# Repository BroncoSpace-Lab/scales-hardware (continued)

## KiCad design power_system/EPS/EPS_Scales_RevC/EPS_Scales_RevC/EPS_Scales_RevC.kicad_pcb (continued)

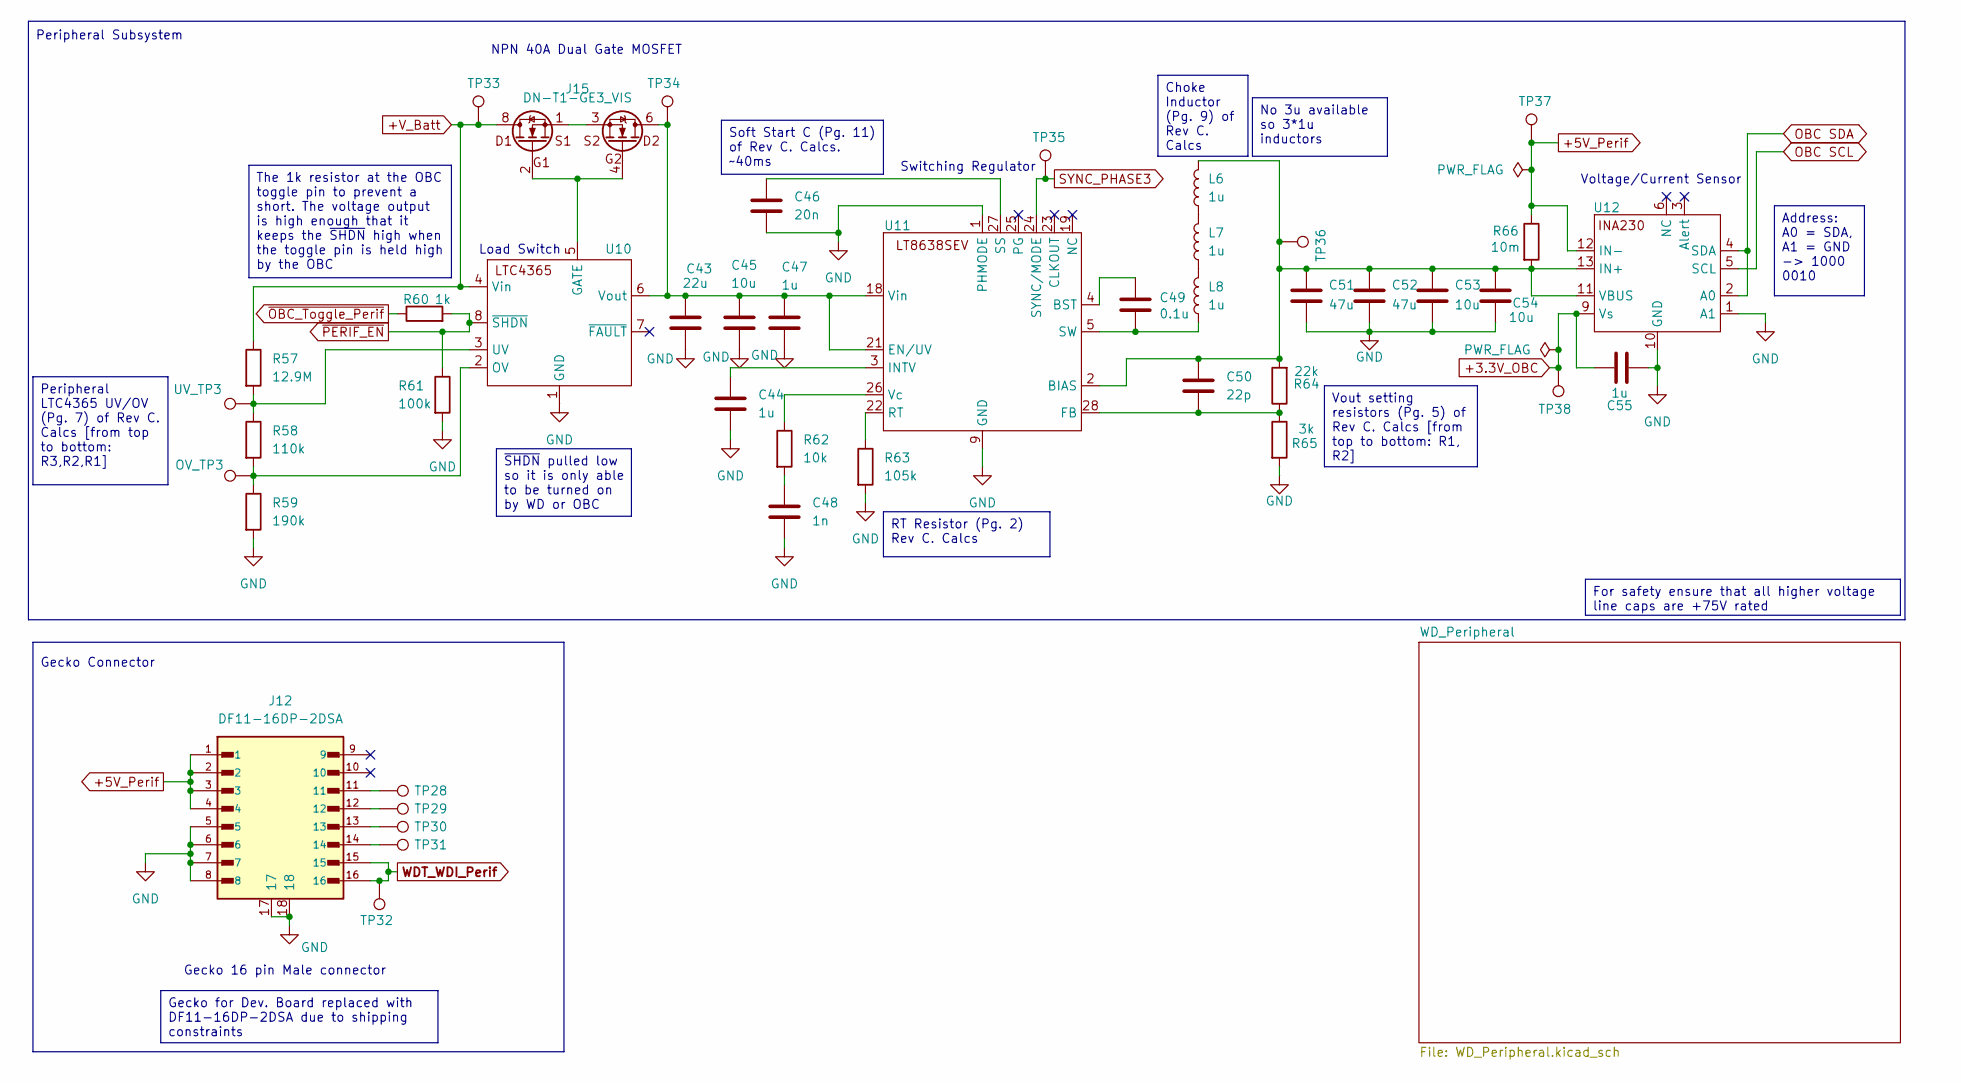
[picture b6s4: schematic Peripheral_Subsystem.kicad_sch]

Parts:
C43: 22u; C_1210_3225Metric; LCSC C309062
C44: 1u; C_0603_1608Metric; LCSC C304010
C45, C53, C54: 10u; C_1210_3225Metric
C46: 20n; C_0603_1608Metric; LCSC C87721
C47, C55: 1u; C_1210_3225Metric; LCSC C304010
C48: 1n; C_0603_1608Metric; LCSC C2173372
C49: 0.1u; C_1210_3225Metric; LCSC C436244
C50: 22p; C_1210_3225Metric
C51, C52: 47u; C_1210_3225Metric
J12: DF11-16DP-2DSA; DF1116DP2DSA08
J15: DN-T1-GE3_VIS; MOSFET_DN-T1-GE3_VIS
L6, L7, L8: 1u; XEL6030102MEC; LCSC C5157561
OV_TP3: TestPoint; TestPoint_Pad_1.0x1.0mm
R57: 12.9M; R_0603_1608Metric
R58: 110k; R_0603_1608Metric; LCSC C25805
R59: 190k; R_0603_1608Metric; LCSC C25811
R60: 1k; R_0603_1608Metric; LCSC C13163
R61: 100k; R_0603_1608Metric; LCSC C14675
R62: 10k; R_0603_1608Metric; LCSC C13564
R63: 105k; R_0603_1608Metric; LCSC C16840
R64: 22k; R_0603_1608Metric; LCSC C23344
R65: 3k; R_0603_1608Metric
R66: 10m; R_2512_6332Metric
TP28, TP29, TP30, TP31, TP32, TP33, TP34, TP35, TP36, TP37, TP38: TestPoint; TestPoint_Pad_1.0x1.0mm
U10: LTC4365; LCSC C580882
U11: LT8638S; LT8638SEVPBF
U12: INA230; INA230AIRGTT
UV_TP3: TestPoint; TestPoint_Pad_1.0x1.0mm

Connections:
+5V_Perif: J12.1, J12.2, J12.3, J12.4, R66.1, TP37.1, U12.12 (IN-); also elsewhere on the board
+V_Batt: J15.7, J15.8, R57.1, TP33.1, U10.4 (Vin); also elsewhere on the board
GND: C43.2, C44.2, C45.2, C46.2, C47.2, C48.2, C51.2, C52.2, C53.2, C54.2, C55.1, J12.5, J12.6, J12.7, J12.8, J12.17, J12.18, R59.2, R61.2, R63.2, R65.2, U10.1 (GND), U11.1 (PHMODE), U11.9 (GND), U12.1 (A1), U12.10 (GND); also elsewhere on the board
unnamed: C48.1, R62.2
unnamed: J12.11, TP28.1
unnamed: J12.12, TP29.1
unnamed: J12.13, TP30.1
unnamed: J12.14, TP31.1
unnamed: J15.1, J15.3
unnamed: L6.1, L7.2
unnamed: L7.1, L8.2
unnamed: J15.2, J15.4, U10.5 (GATE)
unnamed: OV_TP3.1, R58.2, R59.1, U10.2 (OV)
unnamed: R57.2, R58.1, U10.3 (UV), UV_TP3.1
unnamed: C43.1, C45.1, C47.1, J15.5, J15.6, TP34.1, U10.6 (Vout), U11.18 (Vin), U11.21 (EN/UV)
unnamed 93: C50.1, C51.1, C52.1, C53.1, C54.1, L6.2, R64.2, R66.2, TP36.1, U11.2 (BIAS), U12.11 (VBUS), U12.13 (IN+); also elsewhere on the board
unnamed: C49.1, U11.4 (BST)
unnamed 95: C50.2, R64.1, R65.1, U11.28 (FB); also elsewhere on the board
unnamed: C44.1, U11.3 (INTV)
unnamed: R63.1, U11.22 (RT)
unnamed: C46.1, U11.27 (SS)
unnamed 99: C49.2, L8.1, U11.5 (SW); also elsewhere on the board
unnamed: R62.1, U11.26 (Vc)
SYNC_PHASE3: TP35.1, U11.24 (SYNC/MODE); also elsewhere on the board
WDT_WDI_Perif: J12.15, J12.16, TP32.1; also elsewhere on the board
~OBC_Toggle_Perif: R60.1; also elsewhere on the board
~PERIF_EN: R60.2, R61.1, U10.8 (~SHDN); also elsewhere on the board

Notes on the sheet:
NPN 40A Dual Gate MOSFET
Peripheral Subsystem
Load Switch
Switching Regulator
Gecko Connector
Gecko 16 pin Male connector
Voltage/Current Sensor
The 1k resistor at the OBC toggle pin to prevent a short. The voltage output is high enough that it keeps the ~{SHDN} high when the toggle pin is held high by the OBC
Vout setting resistors (Pg. 5) of Rev C. Calcs [from top to bottom: R1, R2]
~{SHDN} pulled low so it is only able to be turned on by WD or OBC
For safety ensure that all higher voltage line caps are +75V rated
Gecko for Dev. Board replaced with DF11-16DP-2DSA due to shipping constraints
Address: A0 = SDA, A1 = GND -> 1000 0010
Soft Start C (Pg. 11) of Rev C. Calcs. ~40ms
No 3u available so 3*1u inductors
Peripheral LTC4365 UV/OV (Pg. 7) of Rev C. Calcs [from top to bottom: R3,R2,R1]
Choke Inductor (Pg. 9) of Rev C. Calcs
RT Resistor (Pg. 2) Rev C. Calcs

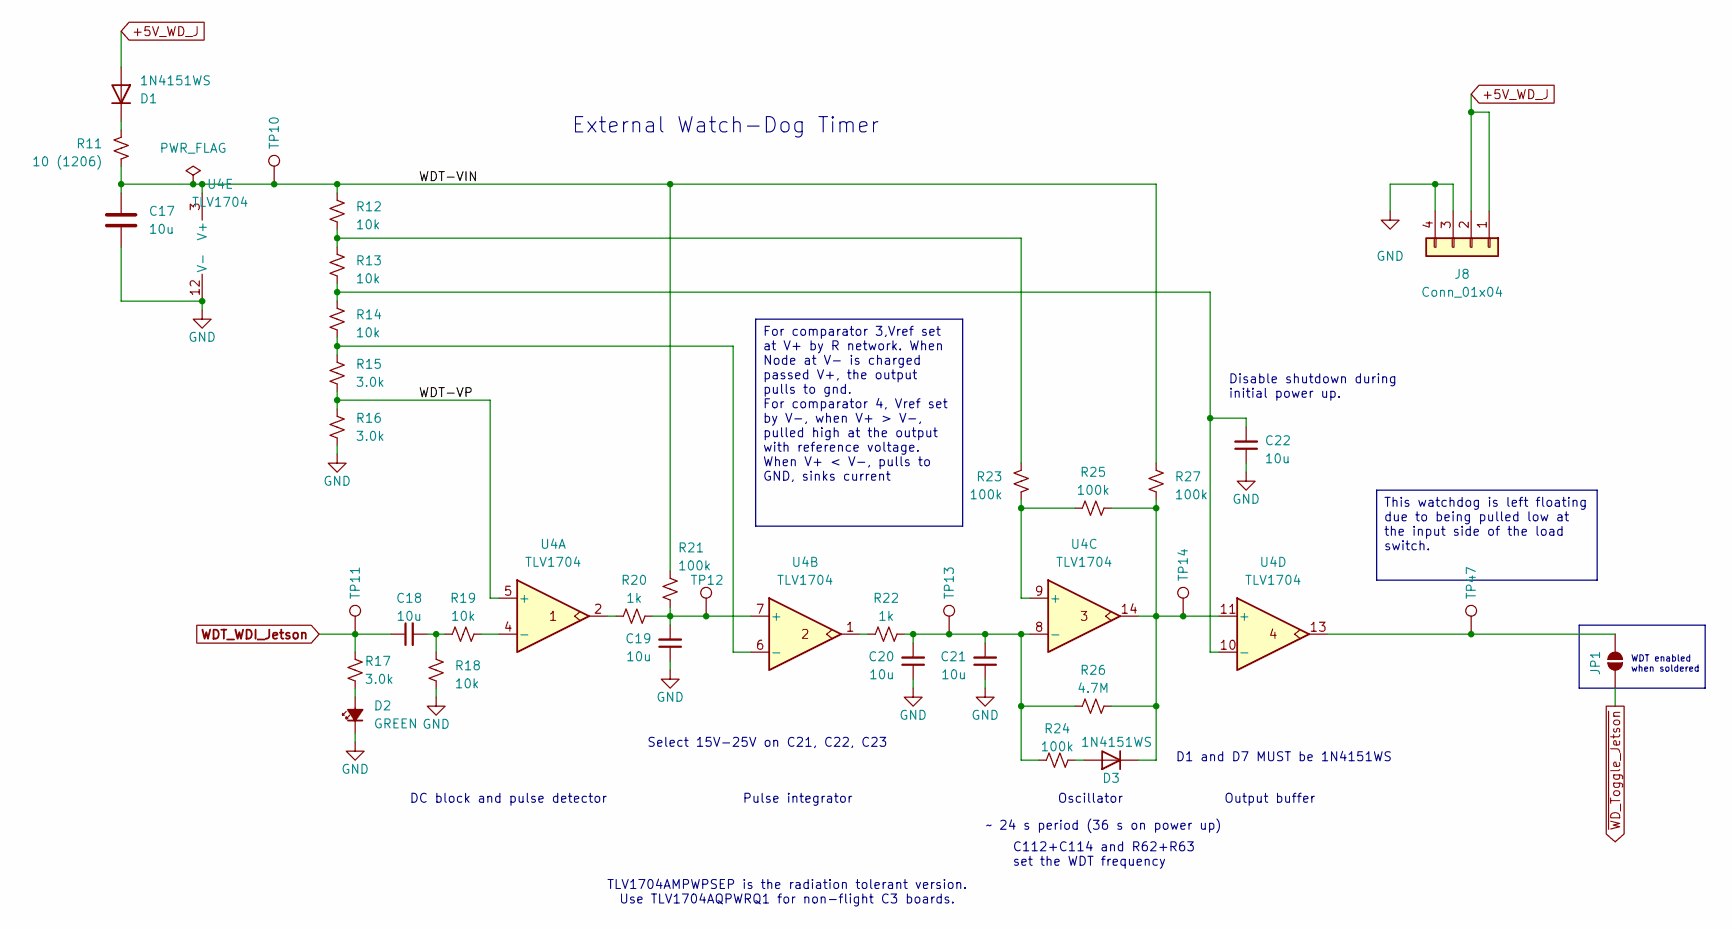
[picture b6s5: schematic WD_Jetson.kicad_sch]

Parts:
C17: 10u; C_1210_3225Metric
C18, C19, C20, C21, C22: 10u; C_1210_3225Metric; MPN GRT188R61C106KE13D
D1, D3: 1N4151WS; SODFL2512X100N; MPN 1N4151WS-E3-08
D2: GREEN; LED_0603_1608Metric; MPN 150060GS75000
J8: Conn_01x04; PinSocket_1x04_P2.54mm_Vertical
JP1: SolderJumper_2_Open; SolderJumper-2_P1.3mm_Open_RoundedPad1.0x1.5mm
R11: 10 (1206); R_1206_3216Metric; MPN ESR18EZPF10R0; LCSC C17903
R12, R13, R14, R18, R19: 10k; R_0603_1608Metric; MPN RMCF0603FT10K0; LCSC C13564
R15, R16, R17: 3.0k; R_0603_1608Metric; MPN RMCF0603FT3K00; LCSC C4211
R20, R22: 1k; R_0603_1608Metric; MPN RMCF0603FT1K00; LCSC C13163
R21, R23, R24, R25, R27: 100k; R_0603_1608Metric; MPN RMCF0603FT100K; LCSC C14675
R26: 4.7M; R_0603_1608Metric; MPN RMCF0603FT4M70
TP10, TP11, TP12, TP13, TP14, TP47: TestPoint; TestPoint_Pad_1.0x1.0mm
U4: TLV1704; TSSOP-14_4.4x5mm_P0.65mm; MPN TLV1704AQPWRQ1; LCSC C181596

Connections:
+5V_WD_J: D1.2 (A), J8.1, J8.2; also elsewhere on the board
/Jetson_Subsystem/WD_Jetson/WDT-VIN: C17.1, R11.2, R12.1, R21.1, R27.2, TP10.1, U4.3 (V+)
/Jetson_Subsystem/WD_Jetson/WDT-VP: R15.2, R16.1, U4.5 (+)
GND: C17.2, C19.1, C20.1, C21.1, C22.1, D2.1 (K), J8.3, J8.4, R16.2, R18.2, U4.12 (V-); also elsewhere on the board
unnamed: C18.2, R18.1, R19.1
unnamed: D1.1 (K), R11.1
unnamed: D2.2 (A), R17.2
unnamed: D3.2 (A), R24.1
unnamed: D3.1 (K), R25.2, R26.1, R27.1, TP14.1, U4.11 (+), U4.14
unnamed: JP1.1 (A), TP47.1, U4.13
unnamed: R12.2, R13.1, R23.2
unnamed: R20.1, U4.2
unnamed: R22.1, U4.1
unnamed: R19.2, U4.4 (-)
unnamed: C19.2, R20.2, R21.2, TP12.1, U4.7 (+)
unnamed: R14.2, R15.1, U4.6 (-)
unnamed: R23.1, R25.1, U4.9 (+)
unnamed: C20.2, C21.2, R22.2, R24.2, R26.2, TP13.1, U4.8 (-)
unnamed: C22.2, R13.2, R14.1, U4.10 (-)
WDT_WDI_Jetson: C18.1, R17.1, TP11.1; also elsewhere on the board
~WD_Toggle_Jetson: JP1.2 (B); also elsewhere on the board

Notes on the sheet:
TLV1704AMPWPSEP is the radiation tolerant version. Use TLV1704AQPWRQ1 for non-flight C3 boards.
Oscillator
External Watch-Dog Timer
Disable shutdown during initial power up.
Pulse integrator
C112+C114 and R62+R63 set the WDT frequency
~ 24 s period (36 s on power up)
D1 and D7 MUST be 1N4151WS
Select 15V-25V on C21, C22, C23
Output buffer
WDT enabled when soldered
DC block and pulse detector
This watchdog is left floating due to being pulled low at the input side of the load switch.
For comparator 3,Vref set at V+ by R network. When Node at V- is charged passed V+, the output pulls to gnd. For comparator 4, Vref set by V-, when V+ > V-, pulled high at the output with reference voltage. When V+ < V-, pulls to GND, sinks current

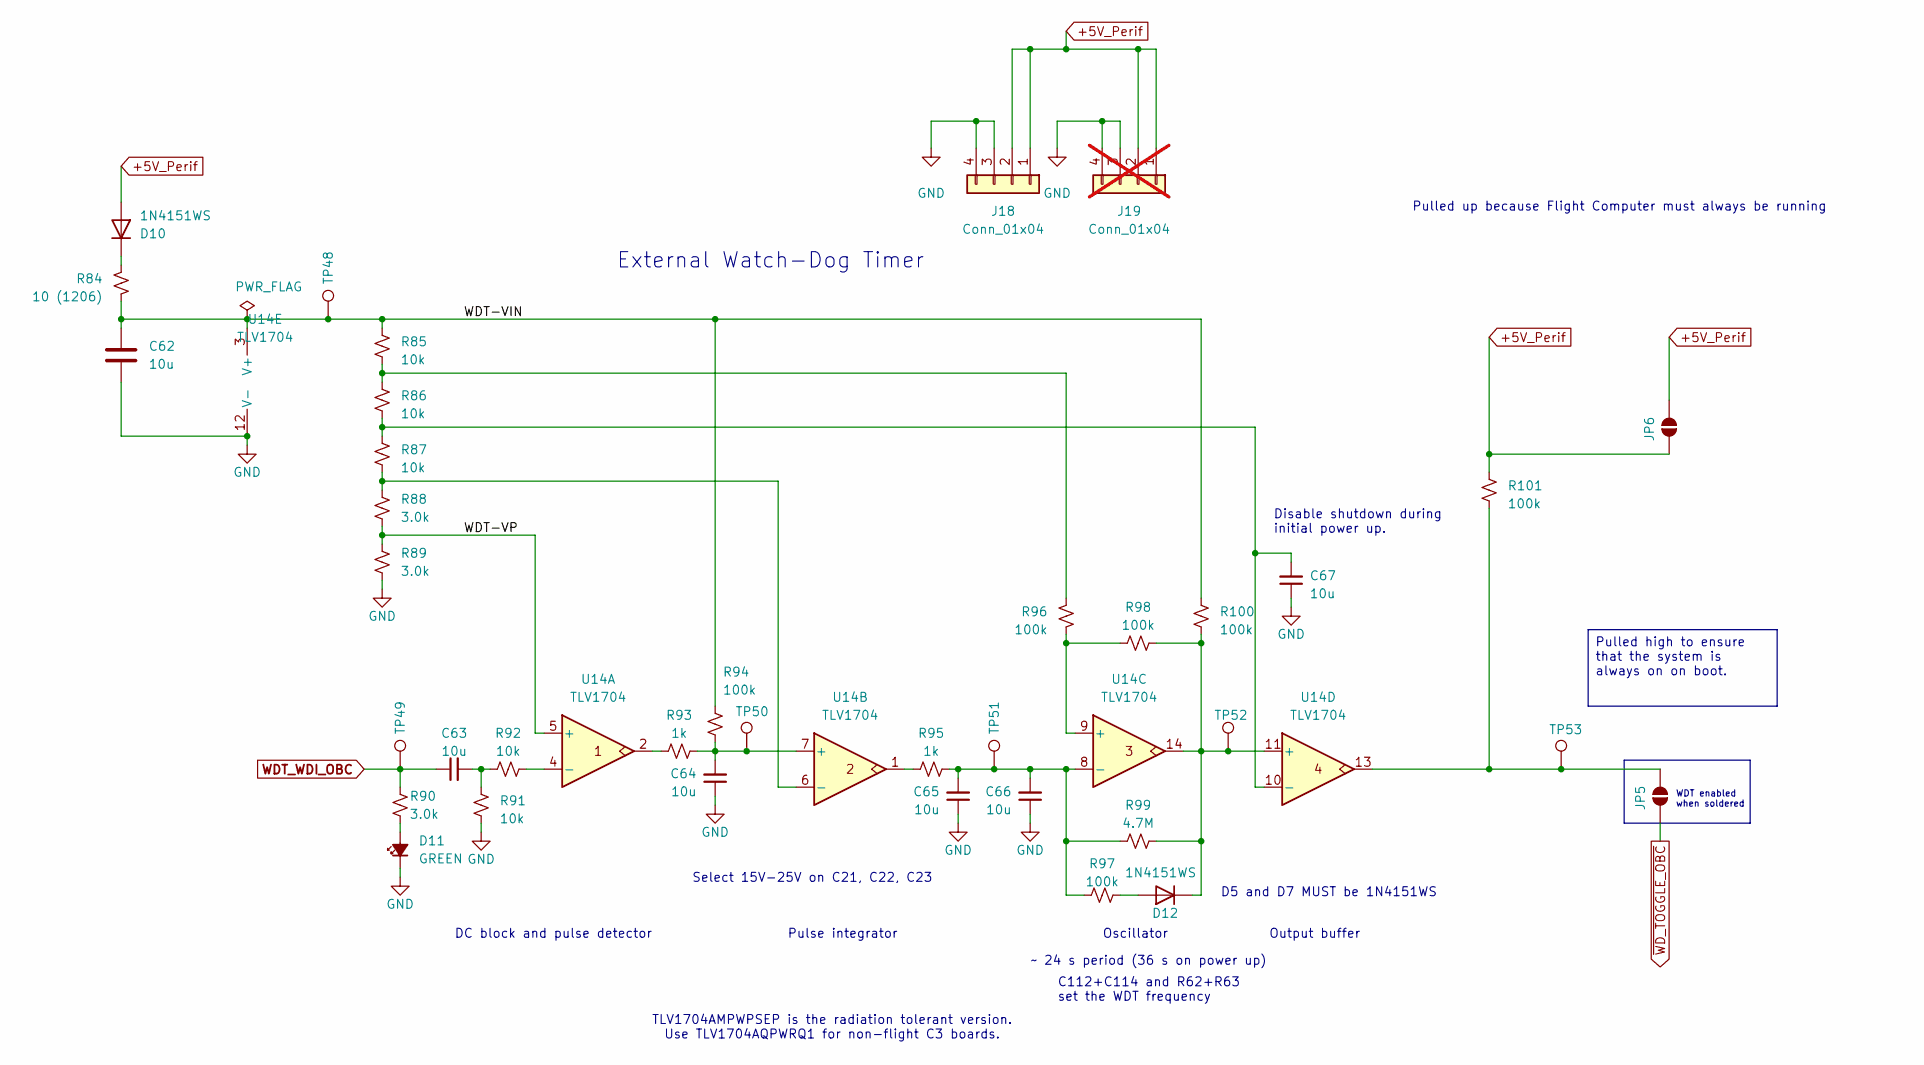
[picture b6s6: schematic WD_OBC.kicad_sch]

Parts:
C62: 10u; C_1210_3225Metric
C63, C64, C65, C66, C67: 10u; C_1210_3225Metric; MPN GRT188R61C106KE13D
D10, D12: 1N4151WS; D_SOD-323; MPN 1N4151WS-E3-08
D11: GREEN; LED_0603_1608Metric; MPN 150060GS75000
J18: Conn_01x04; PinSocket_1x04_P2.54mm_Vertical
J19: Conn_01x04; PinSocket_1x04_P2.54mm_Vertical; not fitted
JP5, JP6: SolderJumper_2_Open; SolderJumper-2_P1.3mm_Open_RoundedPad1.0x1.5mm
R84: 10 (1206); R_1206_3216Metric; MPN ESR18EZPF10R0; LCSC C17903
R85, R86, R87, R91, R92: 10k; R_0603_1608Metric; MPN RMCF0603FT10K0; LCSC C13564
R88, R89, R90: 3.0k; R_0603_1608Metric; MPN RMCF0603FT3K00; LCSC C4211
R93, R95: 1k; R_0603_1608Metric; MPN RMCF0603FT1K00; LCSC C13163
R94, R96, R97, R98, R100, R101: 100k; R_0603_1608Metric; MPN RMCF0603FT100K; LCSC C14675
R99: 4.7M; R_0603_1608Metric; MPN RMCF0603FT4M70
TP48, TP49, TP50, TP51, TP52, TP53: TestPoint; TestPoint_Pad_1.0x1.0mm
U14: TLV1704; TSSOP-14_4.4x5mm_P0.65mm; MPN TLV1704AQPWRQ1; LCSC C181596

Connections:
/OBC_Subsystem/WD_OBC/WDT-VIN: C62.1, R84.2, R85.1, R94.1, R100.2, TP48.1, U14.3 (V+)
/OBC_Subsystem/WD_OBC/WDT-VP: R88.2, R89.1, U14.5 (+)
GND: C62.2, C64.1, C65.1, C66.1, C67.1, D11.1 (K), J18.3, J18.4, J19.3, J19.4, R89.2, R91.2, U14.12 (V-); also elsewhere on the board
unnamed: C63.2, R91.1, R92.1
unnamed: D10.1 (K), R84.1
unnamed: D11.2 (A), R90.2
unnamed: D12.2 (A), R97.1
unnamed: D12.1 (K), R98.2, R99.1, R100.1, TP52.1, U14.11 (+), U14.14
unnamed: JP5.1 (A), R101.1, TP53.1, U14.13
unnamed: R85.2, R86.1, R96.2
unnamed: R93.1, U14.2
unnamed: R95.1, U14.1
unnamed: R92.2, U14.4 (-)
unnamed: C64.2, R93.2, R94.2, TP50.1, U14.7 (+)
unnamed: R87.2, R88.1, U14.6 (-)
unnamed: R96.1, R98.1, U14.9 (+)
unnamed: C65.2, C66.2, R95.2, R97.2, R99.2, TP51.1, U14.8 (-)
unnamed: C67.2, R86.2, R87.1, U14.10 (-)
WDT_WDI_OBC: C63.1, R90.1, TP49.1; also elsewhere on the board
~WD_TOGGLE_OBC: JP5.2 (B); also elsewhere on the board

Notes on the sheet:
Oscillator
Output buffer
DC block and pulse detector
D5 and D7 MUST be 1N4151WS
Disable shutdown during initial power up.
Pulled up because Flight Computer must always be running
Select 15V-25V on C21, C22, C23
Pulse integrator
WDT enabled when soldered
TLV1704AMPWPSEP is the radiation tolerant version. Use TLV1704AQPWRQ1 for non-flight C3 boards.
External Watch-Dog Timer
C112+C114 and R62+R63 set the WDT frequency
~ 24 s period (36 s on power up)
Pulled high to ensure that the system is always on on boot.

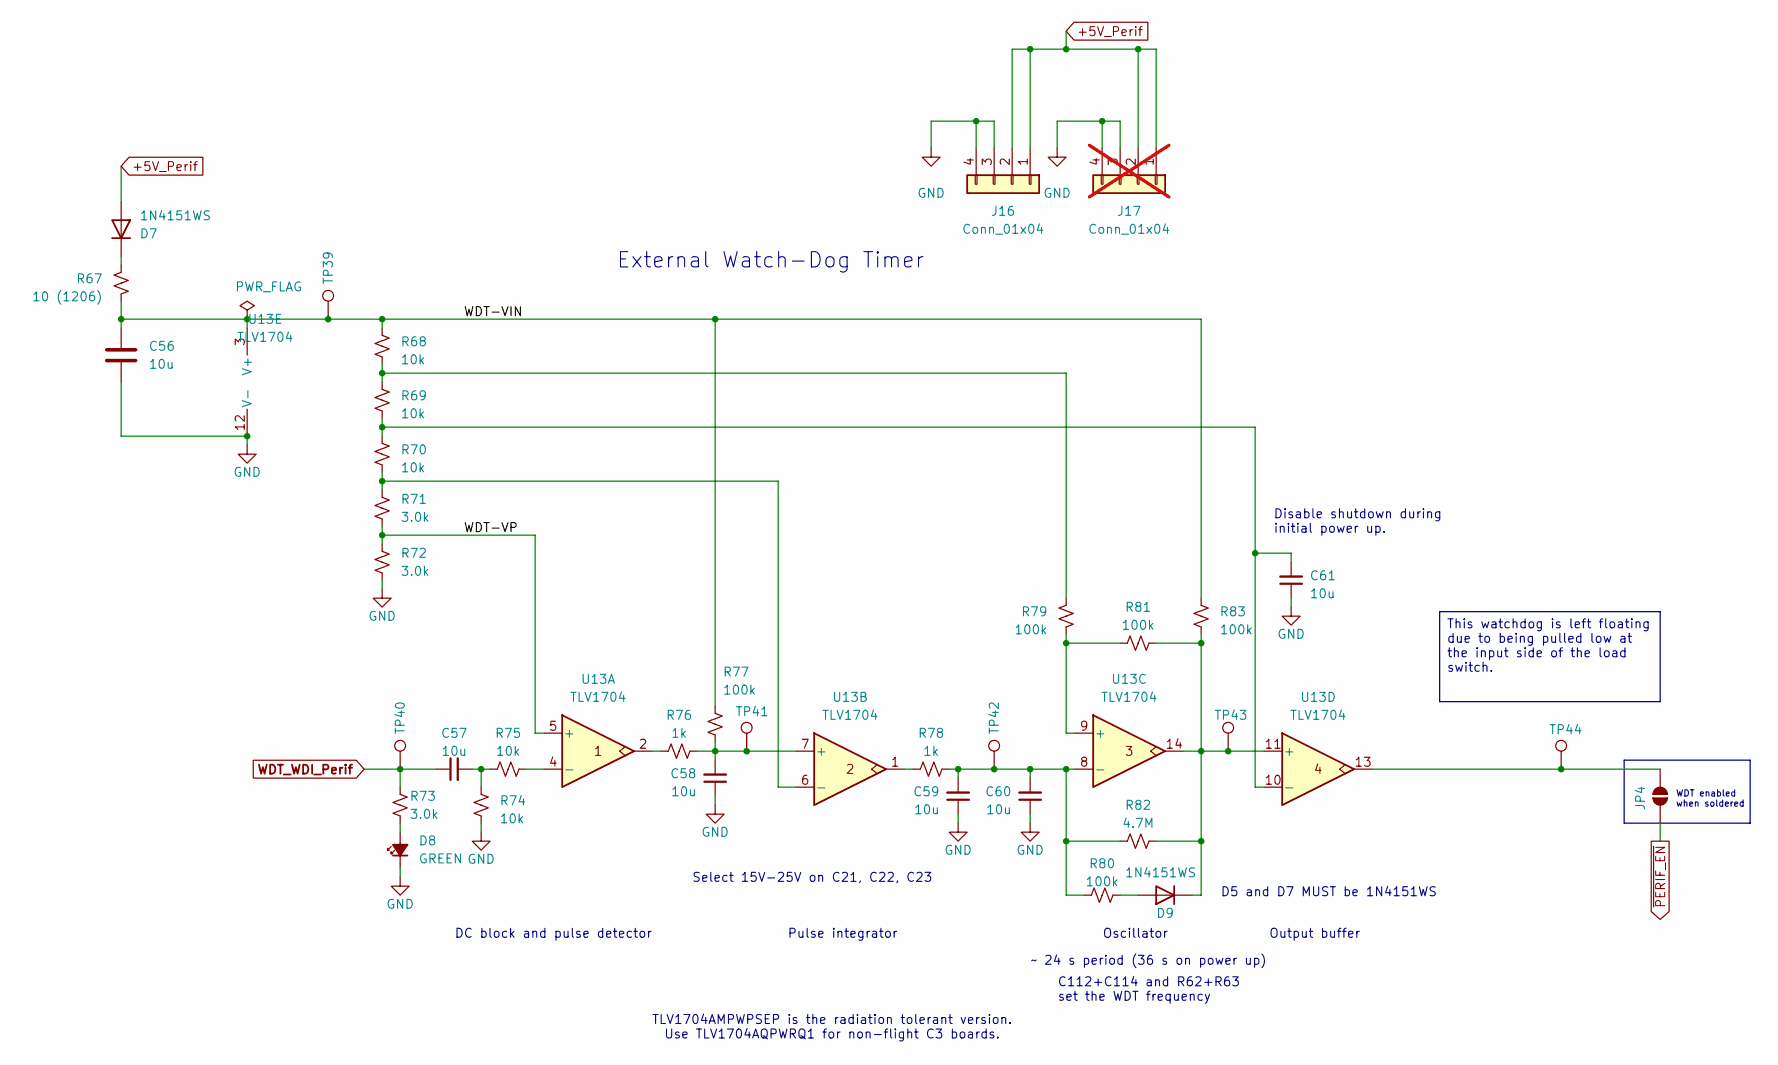
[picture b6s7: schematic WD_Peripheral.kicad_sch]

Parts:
C56: 10u; C_1210_3225Metric
C57, C58, C59, C60, C61: 10u; C_1210_3225Metric; MPN GRT188R61C106KE13D
D7, D9: 1N4151WS; D_SOD-323; MPN 1N4151WS-E3-08
D8: GREEN; LED_0603_1608Metric; MPN 150060GS75000
J16: Conn_01x04; PinSocket_1x04_P2.54mm_Vertical
J17: Conn_01x04; PinSocket_1x04_P2.54mm_Vertical; not fitted
JP4: SolderJumper_2_Open; SolderJumper-2_P1.3mm_Open_RoundedPad1.0x1.5mm
R67: 10 (1206); R_1206_3216Metric; MPN ESR18EZPF10R0; LCSC C17903
R68, R69, R70, R74, R75: 10k; R_0603_1608Metric; MPN RMCF0603FT10K0; LCSC C13564
R71, R72, R73: 3.0k; R_0603_1608Metric; MPN RMCF0603FT3K00; LCSC C4211
R76, R78: 1k; R_0603_1608Metric; MPN RMCF0603FT1K00; LCSC C13163
R77, R79, R80, R81, R83: 100k; R_0603_1608Metric; MPN RMCF0603FT100K; LCSC C14675
R82: 4.7M; R_0603_1608Metric; MPN RMCF0603FT4M70
TP39, TP40, TP41, TP42, TP43, TP44: TestPoint; TestPoint_Pad_1.0x1.0mm
U13: TLV1704; TSSOP-14_4.4x5mm_P0.65mm; MPN TLV1704AQPWRQ1; LCSC C181596

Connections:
+5V_Perif: D7.2 (A), J16.1, J16.2, J17.1, J17.2; also elsewhere on the board
/Peripheral_Subsystem/WD_Peripheral/WDT-VIN: C56.1, R67.2, R68.1, R77.1, R83.2, TP39.1, U13.3 (V+)
/Peripheral_Subsystem/WD_Peripheral/WDT-VP: R71.2, R72.1, U13.5 (+)
GND: C56.2, C58.1, C59.1, C60.1, C61.1, D8.1 (K), J16.3, J16.4, J17.3, J17.4, R72.2, R74.2, U13.12 (V-); also elsewhere on the board
unnamed: C57.2, R74.1, R75.1
unnamed: D7.1 (K), R67.1
unnamed: D8.2 (A), R73.2
unnamed: D9.2 (A), R80.1
unnamed: D9.1 (K), R81.2, R82.1, R83.1, TP43.1, U13.11 (+), U13.14
unnamed: JP4.1 (A), TP44.1, U13.13
unnamed: R68.2, R69.1, R79.2
unnamed: R76.1, U13.2
unnamed: R78.1, U13.1
unnamed: R75.2, U13.4 (-)
unnamed: C58.2, R76.2, R77.2, TP41.1, U13.7 (+)
unnamed: R70.2, R71.1, U13.6 (-)
unnamed: R79.1, R81.1, U13.9 (+)
unnamed: C59.2, C60.2, R78.2, R80.2, R82.2, TP42.1, U13.8 (-)
unnamed: C61.2, R69.2, R70.1, U13.10 (-)
WDT_WDI_Perif: C57.1, R73.1, TP40.1; also elsewhere on the board
~PERIF_EN: JP4.2 (B); also elsewhere on the board

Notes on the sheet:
TLV1704AMPWPSEP is the radiation tolerant version. Use TLV1704AQPWRQ1 for non-flight C3 boards.
Oscillator
External Watch-Dog Timer
Disable shutdown during initial power up.
Pulse integrator
C112+C114 and R62+R63 set the WDT frequency
~ 24 s period (36 s on power up)
D5 and D7 MUST be 1N4151WS
Select 15V-25V on C21, C22, C23
Output buffer
WDT enabled when soldered
DC block and pulse detector
This watchdog is left floating due to being pulled low at the input side of the load switch.

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
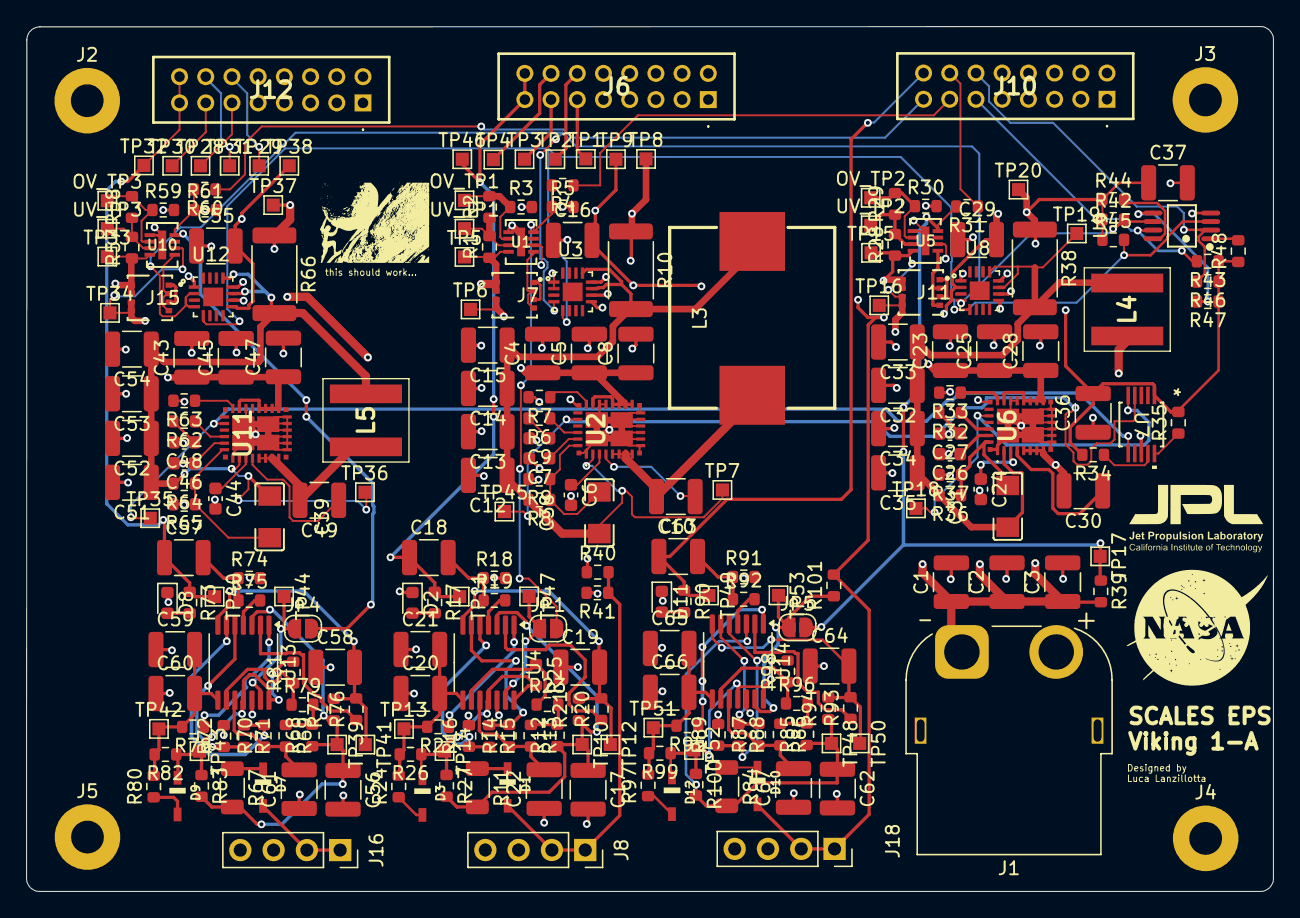
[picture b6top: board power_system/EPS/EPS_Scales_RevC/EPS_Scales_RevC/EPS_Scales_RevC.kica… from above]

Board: 4 copper layers, 95.2 x 66.0 mm, 250 parts (0 on the bottom side), 128 nets.

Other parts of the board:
C39: 22p; C1206
L5: 3.3u; XEL6030

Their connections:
unnamed 93: C39.1, L5.2; also elsewhere on the board
unnamed 95: C39.2; also elsewhere on the board
unnamed 99: L5.1; also elsewhere on the board

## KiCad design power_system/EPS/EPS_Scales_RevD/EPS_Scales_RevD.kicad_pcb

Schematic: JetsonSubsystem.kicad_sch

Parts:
C4: 22n; C0402
C5: 220n; C0402
C10: 10n; C0402
C11, C13, C15, C16: 100n; C0402
C14: 10p; C0402
C54, C55: 47u; CAP-SMD_L7.3-W4.3-FD
D4: LED; LED0603-RD_RED
J6: DF11-16DP-2DSA; CONN-TH_DF11-16DP-2DSA-08; LCSC Part C530981
L1: 4.7u; IND-SMD_L11.0-W10.0
R1, R3, R4, R6, R7, R50: 15k; R0402
R5: 220; R0402
R28: 1k; R0402
R52: 110k; R0402
R53: 47k; R0402
R54: 2k; R0402
R55: 196k; R0402
R56: 10k; R0402
TP1, TP2, TP3, TP4, TP25, TP26, TP27, TP28, TP29, TP38, TP44, TP45, TP46: TestPoint; TestPoint_Pad_1.0x1.0mm
U1: LT8612EUDE#PBF; QFN-28_L6.0-W3.0-P0.50-BL-EP; LCSC Part C580312
U2: INA260AIPWR; TSSOP-16_L5.0-W4.4-P0.65-LS6.4-BL-1; LCSC Part C2155885
U15: TPS1HB08BQPWPRQ1; HTSSOP-16_L5.0-W4.4-P0.65-LS6.4-TL-EP2.9; LCSC Part C3230075

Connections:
+3.3V_OBC: C15.1, U2.10 (VS); also elsewhere on the board
+20V_Jetson: C16.1, J6.1, J6.3, J6.5, J6.7, TP29.1, U2.14 (IN-); also elsewhere on the board
+V_Batt: C5.1, TP25.1, U15.17 (VBB); also elsewhere on the board
GND: C4.2, C5.2, C10.2, C13.2, C15.2, C16.2, C54.2, C55.2, D4.1 (K), J6.9, J6.11, J6.13, J6.15, R1.2, R3.2, R4.2, R6.1, R7.2, R28.1, R52.2, R54.2, R56.2, U1.8 (PGND), U1.11 (GND), U1.25 (NC), U2.4 (A1), U2.5 (A0), U2.6 (GND), U15.1 (GND); also elsewhere on the board
unnamed: D4.2 (A), R5.1
unnamed: J6.2, TP44.1
unnamed: J6.4, TP45.1
unnamed: J6.6, TP1.1
unnamed: J6.8, TP2.1
unnamed: J6.10, TP3.1
unnamed: J6.12, TP4.1
unnamed: C14.1, C54.1, C55.1, L1.2, R55.1, TP28.1, U1.22 (BIAS), U2.1 (IN+), U2.12 (VBUS)
unnamed: C11.1, U1.20 (BST)
unnamed: R53.2, R54.1, U1.4 (EN/UV)
unnamed: C14.2, R55.2, R56.1, U1.24 (FB)
unnamed: C13.1, U1.21 (INTVCC)
unnamed: R52.1, U1.3 (RT)
unnamed: C11.2, L1.1, U1.15 (SW)
unnamed: C10.1, U1.2 (TR/SS)
unnamed: C4.1, R53.1, TP26.1, U1.5 (VIN), U15.6 (VOUT)
unnamed: R7.1, U15.16 (DIA_EN)
unnamed: R6.2, U15.3 (LATCH)
unnamed: R4.1, U15.14 (SEL1)
unnamed: R3.1, U15.15 (SEL2)
unnamed: R28.2, U15.2 (SNS)
unnamed: R5.2, U15.5 (~ST)
OBC_EN_JETSON: R50.1; also elsewhere on the board
SCL: U2.9 (SCL); also elsewhere on the board
SDA: U2.8 (SDA); also elsewhere on the board
SYNC_PHASE3: TP27.1, U1.1 (SYNC); also elsewhere on the board
WDT_WDI_Jetson: J6.14, J6.16, TP46.1; also elsewhere on the board
~WD_EN_JETSON: R1.1, R50.2, TP38.1, U15.4 (EN); also elsewhere on the board

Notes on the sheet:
Jetson Power Subsystem
Gecko Connector
Gecko for Dev. Board replaced with DF11-16DP-2DSA due to shipping constraints
SNS -> 1k -> GND : Not using analog sense Latch -> 15k -> GND : Auto-retry Enabled ~{ST} -> 220 -> LED : Indicates fault when DIA_EN -> GND SEL1 & SEL2 -> 15k -> GND : Diagnostics Disabled (Pg. 5)
To configure: (Pg.8) SYNC (Tied to Clock Phase 2) DONE RT (Set default frequency to 400khz) DONE EN/UV threshold (~24v = UV, due to Li-ion discharge)(Pg. 15) DONE PGND (Tie to GND) DONE SW (Tie to inductor and setup the boost capacitor) DONE BST (add 0.1uF bypass cap) DONE INTVCC (add 0.1uF bypass 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
C10 @10nF ~5ms
R53 and R54 set UVLO @ 24v
R55 and R56 set 20V Vout
A0->GND A1->GND Slave Address 1000000
Vout -> 22nF Cap (Pg. 38)
Vbatt = [24.0, 28.8, 33.6] Due to Li-ion battery charged and discharged states
WD_EN_Jetson is held low at the WD side. If the OBC wants to enable the Jetson board, it must hold the enable line high long enough for the Load Switch, Switching Regulator and Watch dog to power up. Once this is done the WD_EN_PERIF will hold the EN pin high until no pet is recieved. When no pet i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
All Power related caps must +50v 0603/0402. Logic side can be 25V~16V 0402.
L is calculated to be ~5uH, round to whats available, 4.7uH
+20V from EPS to Jetson Vin

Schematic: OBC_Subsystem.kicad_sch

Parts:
C23: 22n; C0402
C24: 220n; C0402
C25: 2.2n; C0402
C26: 10p; C0402
C27, C28, C31, C32: 100n; C0402
C29: 0.1u; C_1210_3225Metric; LCSC C436244
C37: 0.1u; C_1210_3225Metric
C52, C56: 47u; CAP-SMD_L7.3-W4.3-FD
D17: LED; LED0603-RD_RED
J10: DF11-16DP-2DSA; CONN-TH_DF11-16DP-2DSA-08; LCSC Part C530981
L2: 8.2u; IND-SMD_L11.5-W10.0; LCSC C149543
R34: 14k; R_0603_1608Metric
R35: 17k; R_0603_1608Metric
R41, R59, R60, R61: 15k; R0402
R42, R43, R44, R45, R46, R47, R48: 4.7k; R_0603_1608Metric
R57: 1k; R0402
R58: 220; R0402
R62: 110k; R0402
R63: 47k; R0402
R64: 2k; R0402
R65: 240k; R0402
R66, R108: 10k; R0402
R107: 56.2k; R0402
TP22, TP23, TP24, TP31, TP32, TP33, TP34, TP35, TP36: TestPoint; TestPoint_Pad_1.0x1.0mm
U3: LT8612EUDE#PBF; QFN-28_L6.0-W3.0-P0.50-BL-EP; LCSC Part C580312
U5: INA260AIPWR; TSSOP-16_L5.0-W4.4-P0.65-LS6.4-BL-1; LCSC Part C2155885
U7: LTC6902; MSOP-10_L3.0-W3.0-P0.50-LS5.0-BL; LCSC C581012
U9: TCA4307DGKR; VSSOP-8_L3.0-W3.0-P0.65-LS4.9-BL; LCSC Part C880333
U17: TPS1HB08BQPWPRQ1; HTSSOP-16_L5.0-W4.4-P0.65-LS6.4-TL-EP2.9; LCSC Part C3230075

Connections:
+3.3V_OBC: C29.2, C31.1, C32.1, C37.1, J10.1, J10.3, J10.5, J10.7, R34.1, R35.1, R42.1, R43.1, R44.1, R45.1, R46.1, R47.1, R48.1, TP34.1, U5.5 (A0), U5.10 (VS), U5.14 (IN-), U7.1 (V+); also elsewhere on the board
+V_Batt: C24.1, R107.2, TP31.1, U17.17 (VBB); also elsewhere on the board
GND: C23.2, C24.2, C25.2, C28.2, C29.1, C31.2, C32.2, C37.2, C52.2, C56.2, D17.1 (K), J10.9, J10.11, J10.13, J10.15, R41.1, R57.1, R59.2, R60.2, R61.2, R62.2, R64.2, R66.2, R108.1, U3.8 (PGND), U3.11 (GND), U3.25 (NC), U5.4 (A1), U5.6 (GND), U7.8 (GND), U9.4 (GND), U17.1 (GND); also elsewhere on the board
unnamed: D17.2 (A), R58.1
unnamed: J10.2, TP22.1
unnamed: J10.4, TP23.1
unnamed: J10.10, TP24.1
unnamed: C26.1, C52.1, C56.1, L2.2, R65.1, TP33.1, U3.22 (BIAS), U5.1 (IN+), U5.12 (VBUS)
unnamed: C27.1, U3.20 (BST)
unnamed: R63.2, R64.1, U3.4 (EN/UV)
unnamed: C26.2, R65.2, R66.1, U3.24 (FB)
unnamed: C28.1, U3.21 (INTVCC)
unnamed: R62.1, U3.3 (RT)
unnamed: C27.2, L2.1, U3.15 (SW)
unnamed: C25.1, U3.2 (TR/SS)
unnamed: R34.2, U7.9 (MOD)
unnamed: R35.2, U7.10 (SET)
unnamed: R48.2, U9.1 (EN)
unnamed: R47.2, U9.5 (READY)
unnamed: R44.2, U9.8 (VCC)
unnamed: R59.1, U17.16 (DIA_EN)
unnamed: R41.2, U17.3 (LATCH)
unnamed: R61.1, U17.14 (SEL1)
unnamed: R60.1, U17.15 (SEL2)
unnamed: R57.2, U17.2 (SNS)
unnamed: C23.1, R63.1, TP32.1, U3.5 (VIN), U17.6 (VOUT)
unnamed: R58.2, U17.5 (~ST)
OBC SCL: J10.8, R46.2, U9.2 (SCLOUT)
OBC SDA: J10.6, R43.2, U9.7 (SDAOUT)
OBC_EN_JETSON: J10.12; also elsewhere on the board
OBC_EN_PERIF: J10.14; also elsewhere on the board
SCL: R45.2, U5.9 (SCL), U9.3 (SCLIN); also elsewhere on the board
SDA: R42.2, U5.8 (SDA), U9.6 (SDAIN); also elsewhere on the board
SYNC_PHASE1: TP35.1, U3.1 (SYNC), U7.4 (OUT1)
SYNC_PHASE2: U7.5 (OUT2); also elsewhere on the board
SYNC_PHASE3: U7.6 (OUT3); also elsewhere on the board
WDT_WDI_OBC: J10.16; also elsewhere on the board
~WD_EN_OBC: R107.1, R108.2, TP36.1, U17.4 (EN); also elsewhere on the board

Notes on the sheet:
Clock
OBC Subsystem
I2C Buffer
Gecko Connector
Gecko 16 pin Male connector
R65 and R66 set 3.3V Vout
L is calculated to 8.7u round to whats avaialable 8.2uH
A0->Vs A1->GND Slave Address 1000001
All Power related caps must +50v 0603/0402. Logic side can be 25V~16V 0402.
To configure: (Pg.8) SYNC (Tied to Clock Phase 2) DONE RT (Set default frequency to 400khz) DONE EN/UV threshold (~24v = UV, due to Li-ion discharge)(Pg. 15) DONE PGND (Tie to GND) DONE SW (Tie to inductor and setup the boost capacitor) (Pg. 13) DONE BST (add 0.1uF bypass cap) DONE INTVCC (add 0.1u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
Vbatt = [24.0, 28.8, 33.6] Due to Li-ion battery charged and discharged states
Safe resistor divider to ensure at both high and low Lipo levels OBC is always on.
WD_EN is pulled high on WD side. OBC is always on. If the OBC WD is not pet, it will pull low, temporarily triggering a low at EN.
R63 and R64 set UVLO @ 24v
Vout -> 22nF Cap (Pg. 38)
C25 @2.2nF ~1ms
Gecko for Dev. Board replaced with DF11-16DP-2DSA due to shipping constraints
SNS -> 1k -> GND : Not using analog sense Latch -> 15k -> GND : Auto-retry Enabled ~{ST} -> 220 -> LED : Indicates fault when DIA_EN -> GND SEL1 & SEL2 -> 15k -> GND : Diagnostics Disabled (Pg. 5)
Clock to go be powered with OBC. Set to 400Khz, SSFM on. 3 Phase setting

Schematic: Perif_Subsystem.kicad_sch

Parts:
C36: 22n; C0402
C38: 220n; C0402
C39: 2.2n; C0402
C40, C41, C50, C51: 100n; C0402
C48, C53: 47u; CAP-SMD_L7.3-W4.3-FD
C49: 10p; C0402
CN1: DF11-16DP-2DSA(08); CONN-TH_DF11-16DP-2DSA-08; LCSC Part C530981
D9: LED; LED0603-RD_RED
L3: 12u; IND-SMD_L13.5-W12.6; LCSC C5339468
R72, R76, R79, R80, R81, R82: 15k; R0402
R75: 1k; R0402
R77: 220; R0402
R83: 47k; R0402
R101: 2k; R0402
R102: 110k; R0402
R103: 20.8k; R0402
R104: 5k; R0402
TP16, TP17, TP18, TP19, TP20, TP21, TP37, TP39, TP40, TP41, TP42, TP43: TestPoint; TestPoint_Pad_1.0x1.0mm
U12: TPS1HB08BQPWPRQ1; HTSSOP-16_L5.0-W4.4-P0.65-LS6.4-TL-EP2.9; LCSC Part C3230075
U13: LT8612EUDE#PBF; QFN-28_L6.0-W3.0-P0.50-BL-EP; LCSC Part C580312
U16: INA260AIPWR; TSSOP-16_L5.0-W4.4-P0.65-LS6.4-BL-1; LCSC Part C2155885

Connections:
+3.3V_OBC: C50.1, U16.4 (A1), U16.5 (A0), U16.10 (VS); also elsewhere on the board
+5V_Perif: C51.1, CN1.1, CN1.3, CN1.5, CN1.7, TP43.1, U16.14 (IN-); also elsewhere on the board
+V_Batt: C38.1, TP39.1, U12.17 (VBB); also elsewhere on the board
GND: C36.2, C38.2, C39.2, C41.2, C48.2, C50.2, C51.2, C53.2, CN1.9, CN1.11, CN1.13, CN1.15, D9.1 (K), R72.2, R75.2, R76.2, R79.2, R80.2, R81.2, R101.2, R102.2, R104.2, U12.1 (GND), U13.8 (PGND), U13.11 (GND), U13.25 (NC), U16.6 (GND); also elsewhere on the board
unnamed: CN1.4, TP16.1
unnamed: CN1.6, TP17.1
unnamed: CN1.8, TP18.1
unnamed: CN1.10, TP19.1
unnamed: CN1.12, TP20.1
unnamed: CN1.14, TP21.1
unnamed: D9.2 (A), R77.2
unnamed: R81.1, U12.16 (DIA_EN)
unnamed: R76.1, U12.3 (LATCH)
unnamed: R80.1, U12.14 (SEL1)
unnamed: R79.1, U12.15 (SEL2)
unnamed: R75.1, U12.2 (SNS)
unnamed: C36.1, R83.1, TP40.1, U12.6 (VOUT), U13.5 (VIN)
unnamed: R77.1, U12.5 (~ST)
unnamed: C48.1, C49.1, C53.1, L3.2, R103.1, TP42.1, U13.22 (BIAS), U16.1 (IN+), U16.12 (VBUS)
unnamed: C40.1, U13.20 (BST)
unnamed: R83.2, R101.1, U13.4 (EN/UV)
unnamed: C49.2, R103.2, R104.1, U13.24 (FB)
unnamed: C41.1, U13.21 (INTVCC)
unnamed: R102.1, U13.3 (RT)
unnamed: C40.2, L3.1, U13.15 (SW)
unnamed: C39.1, U13.2 (TR/SS)
OBC_EN_PERIF: R82.1; also elsewhere on the board
SCL: U16.9 (SCL); also elsewhere on the board
SDA: U16.8 (SDA); also elsewhere on the board
SYNC_PHASE2: TP41.1, U13.1 (SYNC); also elsewhere on the board
WDT_WDI_Perif: CN1.16; also elsewhere on the board
~WD_EN_PERIF: R72.1, R82.2, TP37.1, U12.4 (EN); also elsewhere on the board

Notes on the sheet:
Gecko 16 pin Male connector
Peripheral Subsystem
Gecko Connector
A0->Vs A1->VS Slave Address 1000101
R103 and R104 set 5V Vout
L is calculated to 12.95, round to whats available, 12uH
Vbatt = [24.0, 28.8, 33.6] Due to Li-ion battery charged and discharged states
To configure: (Pg.8) SYNC (Tied to Clock Phase 2) DONE RT (Set default frequency to 400khz) DONE EN/UV threshold (~24v = UV, due to Li-ion discharge)(Pg. 15) DONE PGND (Tie to GND) DONE SW (Tie to inductor and setup the boost capacitor) (Pg. 13) DONE BST (add 0.1uF bypass cap) DONE INTVCC (add 0.1u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
C25 @2.2nF ~1ms
R83 and R101 set UVLO @ 24v
Vout -> 22nF Cap (Pg. 38)
SNS -> 1k -> GND : Not using analog sense Latch -> 15k -> GND : Auto-retry Enabled ~{ST} -> 220 -> LED : Indicates fault when DIA_EN -> GND SEL1 & SEL2 -> 15k -> GND : Diagnostics Disabled (Pg. 5)
Gecko for Dev. Board replaced with DF11-16DP-2DSA due to shipping constraints
All Power related caps must +50v 0603/0402. Logic side can be 25V~16V 0402.

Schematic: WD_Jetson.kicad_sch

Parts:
C18, C19, C20, C21, C22: 10u; C_1210_3225Metric; MPN GRT188R61C106KE13D
C45, C46, C47: 220u; CAP-SMD_BD6.3-L6.6-W6.6-FD; LCSC Part C171665
D1, D3: 1N4151WS; SOD2512X116N; MPN 1N4151WS-E3-08
D2: GREEN; LED_0603_1608Metric; MPN 150060GS75000
J8: Conn_01x04; PinSocket_1x04_P2.54mm_Vertical
JP1: SolderJumper_2_Open; SolderJumper-2_P1.3mm_Open_RoundedPad1.0x1.5mm
R11: 10 (1206); R_1206_3216Metric; MPN ESR18EZPF10R0; LCSC C17903
R12, R13, R14, R18, R19: 10k; R_0603_1608Metric; MPN RMCF0603FT10K0; LCSC C13564
R15, R16, R17: 3.0k; R_0603_1608Metric; MPN RMCF0603FT3K00; LCSC C4211
R20, R22: 1k; R_0603_1608Metric; MPN RMCF0603FT1K00; LCSC C13163
R21, R23, R24, R25, R27: 100k; R_0603_1608Metric; MPN RMCF0603FT100K; LCSC C14675
R26: 4.7M; R_0603_1608Metric; MPN RMCF0603FT4M70
TP10, TP11, TP12, TP13, TP14, TP47: TestPoint; TestPoint_Pad_1.0x1.0mm
U4: TLV1704; TSSOP-14_4.4x5mm_P0.65mm; MPN TLV1704AQPWRQ1; LCSC C181596

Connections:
+20V_Jetson: D1.2 (A), J8.1, J8.2; also elsewhere on the board
/Jetson_Subsystem/WD_Jetson/WDT-VIN: C45.1, C46.1, C47.1, R11.2, R12.1, R21.1, R27.2, TP10.1, U4.3 (V+)
/Jetson_Subsystem/WD_Jetson/WDT-VP: R15.2, R16.1, U4.5 (+)
GND: C19.1, C20.1, C21.1, C22.1, C45.2, C46.2, C47.2, D2.1 (K), J8.3, J8.4, R16.2, R18.2, U4.12 (V-); also elsewhere on the board
unnamed: C18.2, R18.1, R19.1
unnamed: D1.1 (K), R11.1
unnamed: D2.2 (A), R17.2
unnamed: D3.2 (A), R24.1
unnamed: D3.1 (K), R25.2, R26.1, R27.1, TP14.1, U4.11 (+), U4.14
unnamed: JP1.1 (A), TP47.1, U4.13
unnamed: R12.2, R13.1, R23.2
unnamed: R20.1, U4.2
unnamed: R22.1, U4.1
unnamed: R19.2, U4.4 (-)
unnamed: C19.2, R20.2, R21.2, TP12.1, U4.7 (+)
unnamed: R14.2, R15.1, U4.6 (-)
unnamed: R23.1, R25.1, U4.9 (+)
unnamed: C20.2, C21.2, R22.2, R24.2, R26.2, TP13.1, U4.8 (-)
unnamed: C22.2, R13.2, R14.1, U4.10 (-)
WDT_WDI_Jetson: C18.1, R17.1, TP11.1; also elsewhere on the board
~WD_EN_JETSON: JP1.2 (B); also elsewhere on the board

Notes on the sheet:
TLV1704AMPWPSEP is the radiation tolerant version. Use TLV1704AQPWRQ1 for non-flight C3 boards.
Oscillator
External Watch-Dog Timer
Disable shutdown during initial power up.
Pulse integrator
C112+C114 and R62+R63 set the WDT frequency
~ 24 s period (36 s on power up)
D1 and D7 MUST be 1N4151WS
Select 15V-25V on C21, C22, C23
Output buffer
WDT enabled when soldered
DC block and pulse detector
Pulled down. Holds Jetson off Until WD is enabled and the WD_EN goes high.
WD_EN_Jetson goes to EN of the load switch controller
For comparator 3,Vref set at V+ by R network. When Node at V- is charged passed V+, the output pulls to gnd. For comparator 4, Vref set by V-, when V+ > V-, pulled high at the output with reference voltage. When V+ < V-, pulls to GND, sinks current
660uF Capacitance used to keep WD output high after reset for 2-3s to allow for subsystem reboot
